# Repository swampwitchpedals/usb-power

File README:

# USB POWER

Have you ever needed to power a guitar pedal at your desk? What about on the go? Maybe you're away from your board and you just want to test something out, but you've got no power bank.

Enter the USB power converter. This USB-A plugin device provides a 9V(ish) power source to a [standard DC power jack](link here) so that you can power a pedal in any situation.

## Project Details
Includes a zip file of gerber data for the PCB, as well as BOM and Pick'n'Place files for JLCPCB. [All files found here]().

## Technical Details
The chip on this board is the [LTC660](https://www.analog.com/media/en/technical-documentation/data-sheets/660fa.pdf), a low-power CMOS charge pump that can provide up to 100mA of current. The basic schematic is taken from the datasheet 
[[./datasheet.png]]

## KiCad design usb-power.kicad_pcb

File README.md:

# USB POWER

Have you ever needed to power a guitar pedal at your desk? What about on the go? Maybe you're away from your board and you just want to test something out, but you've got no power bank.

Enter the USB power converter. This USB-A plugin device provides a 9V(ish) power source to a [standard DC power jack](https://www.sparkfun.com/products/119) so that you can power a pedal in any situation.

## Project Details
Includes a zip file of gerber data for the PCB, as well as BOM and Pick'n'Place files for JLCPCB. [All files found here]().

## Technical Details
The chip on this board is the [LTC660](https://www.analog.com/media/en/technical-documentation/data-sheets/660fa.pdf), a low-power CMOS charge pump that can provide up to 100mA of current. The basic schematic is taken from the datasheet

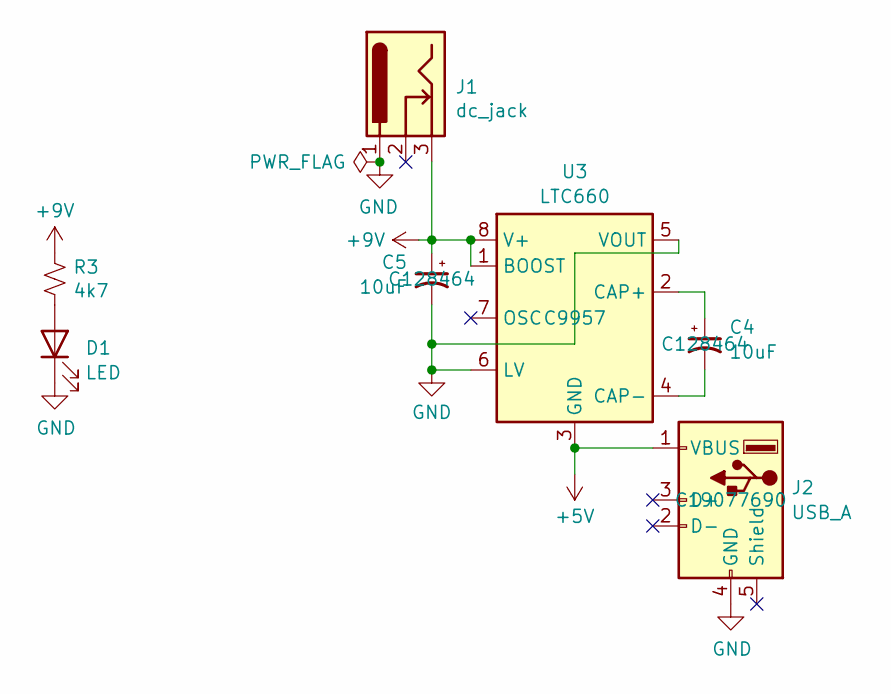
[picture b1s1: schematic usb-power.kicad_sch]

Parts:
C4, C5: 10uF; CP_Elec_6.3x5.4; LCSC C128464
D1: LED; LED_0805_2012Metric
J1: dc_jack; power_jack
J2: USB_A; USB A RAPHCUA20E; LCSC C19077690
R3: 4k7; R_0603
U3: LTC660; SOIC-8_3.9x4.9mm_P1.27mm; LCSC C9957

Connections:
+5V: J2.1 (VBUS), U3.3 (GND)
+9V: C5.1, J1.3, R3.2, U3.1 (BOOST), U3.8 (V+)
GND: C5.2, D1.1 (K), J1.1, J2.4 (GND), U3.5 (VOUT), U3.6 (LV)
unnamed: D1.2 (A), R3.1
unnamed: C4.1, U3.2 (CAP+)
unnamed: C4.2, U3.4 (CAP-)

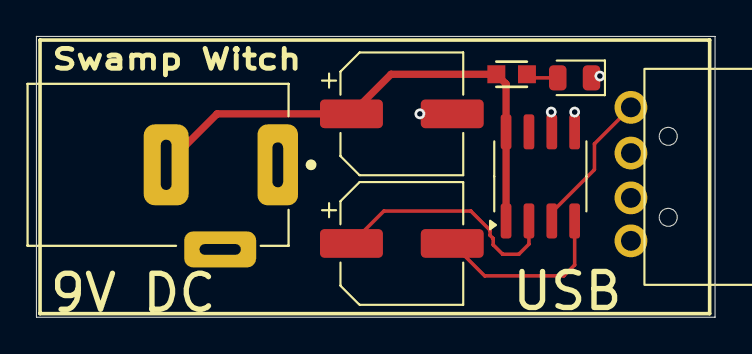
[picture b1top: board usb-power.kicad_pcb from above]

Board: 2 copper layers, 37.7 x 15.6 mm, 7 parts (0 on the bottom side), 6 nets.
